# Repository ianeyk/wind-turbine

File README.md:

# wind-turbine
Working repo for summer research on the Just Energy Hub wind turbine design.

## GitHub Repo Index
* **Small_wind_turbine**
    * **3_phase_generator_buck_converter.plecs:** Main working PLECS model for the small turbine buck converter
    * **Frequency_analysis_buck_converter**
        * Contains four additional PLECS models which were used to run bode plots for designing the compensator circuit for the small wind turbine.
    * **Small_turbine_buck_converter_parameters**
        * **Buck_converter_parameters.ipynb:** Jupyter Notebook containing calculations for the inductor value and compensator circuit.
        * **Buck_converter_parameters.html:** Exported HTML of same Notebook
        * **Buck_converter_parameters.pdf:** Exported PDF of same Notebook
        * **Plecs_helper.py:** Library of helper functions used in the Notebook
    * **Small_buck_converter_design_calculations**
        * **Design_calculations.ipynb, html, pdf:** Secondary notebook for calculating such things as how much current the turbine can supply at safe rotation speeds, specs for the input capacitance value, slew rate to ensure the diff amps can respond fast enough, and resistor values for the indicator LEDs.
    * **KiCAD:** Contains the schematic and layout for the small-scale buck converter PCB board which I designed and manufactured over the summer.
* **Large_wind_turbine**
    * **siemens_model_buck_converter_v1.plecs:** Main working PLECS model for the large turbine buck converter, including the 1FW3208-1EE model of the physical generator. The only things that are different between this model and the small_wind_turbine model are the inductor value, compensator values, and perhaps the input capacitance.
     * **1_kv_3phase_generator_buck_converter.plecs:** Older model without using the 1FW3208-1EE model.
    * **Frequency_analysis_buck_converter**
        * Contains four additional PLECS models which were used to run bode plots for designing the compensator circuit for the large wind turbine.
    * **Large_turbine_buck_converter_parameters**
        * **Buck_converter_parameters.ipynb:** Jupyter Notebook containing calculations for the inductor value and compensator circuit.
        * **Minimum_conversion_ratio.ipynb:** Jupyter Notebook containing calculations for the minimum switching time given a 1kV-12V buck converter voltage ratio. I concluded that this is perfectly feasible given a 10kHz switching frequency.
    * **KiCAD:** Folder containing duplicates of the small wind turbine KiCAD files. I was going to start with a copy and modify it, but I never got around to starting it.
    * **LTspice:** Contains a single LTspice model verifying that the bootstrap gate driver will work.
* **Generic_wind_turbine**
    * Earlier exploratory work which served as a template for the above analyses. It should probably be moved to the Archive folder.
* **Measurements_and_calculations**
    * **Battery_measurements**
        * **Battery_resistance.ipynb, .html, .pdf:** Jupyter Notebook analyzing a small set of data I took on our 12V marine batteries in the lab to quantify the internal resistance.
    * **Generator_volage**
        * **Generator_voltage.ipynb, .html, .pdf:** Jupyter Notebook plotting the results of putting the small test turbine in front of the wind tunnel. It calculates the frequency and voltage amplitude at various wind speeds.
    * **Large_turbine_power_predictions**
        * **Large_turbine_power_predictions.ipyny, .html, .pdf:** Jupyter Notebook and exported versions analyzing the power generation data from one of the Eastern Wind Power documents as well as a PLECS model for the generator and the anemometer data from Olin's campus. I recommend a cut-out wind speed of 12m/s for the large turbine.
* **Charge_controller_code**
    * **Platformio.ini:** Platformio project for code running on the Adafruit Feather Adalogger board attached to the small-scale buck converter PCB I designed and manufactured this summer.
    * **src/main.cpp:** Main code file containing Arduino language to be uploaded to the Feather.
* **Archive**
    * **Generator_internal_resistance**
        * **Internal_resistance.ipynb, .html, .pdf:** Jupyter Notebook for an initial experiment determining the internal resistance of the small generator by hand-spinning the small turbine and watching the frequency and voltage decay as it slowed down. The internal resistance calculations match those in *Generator_voltage.ipynb*, and that notebook also has further relevant calculations. Hence this notebook is in the archive.

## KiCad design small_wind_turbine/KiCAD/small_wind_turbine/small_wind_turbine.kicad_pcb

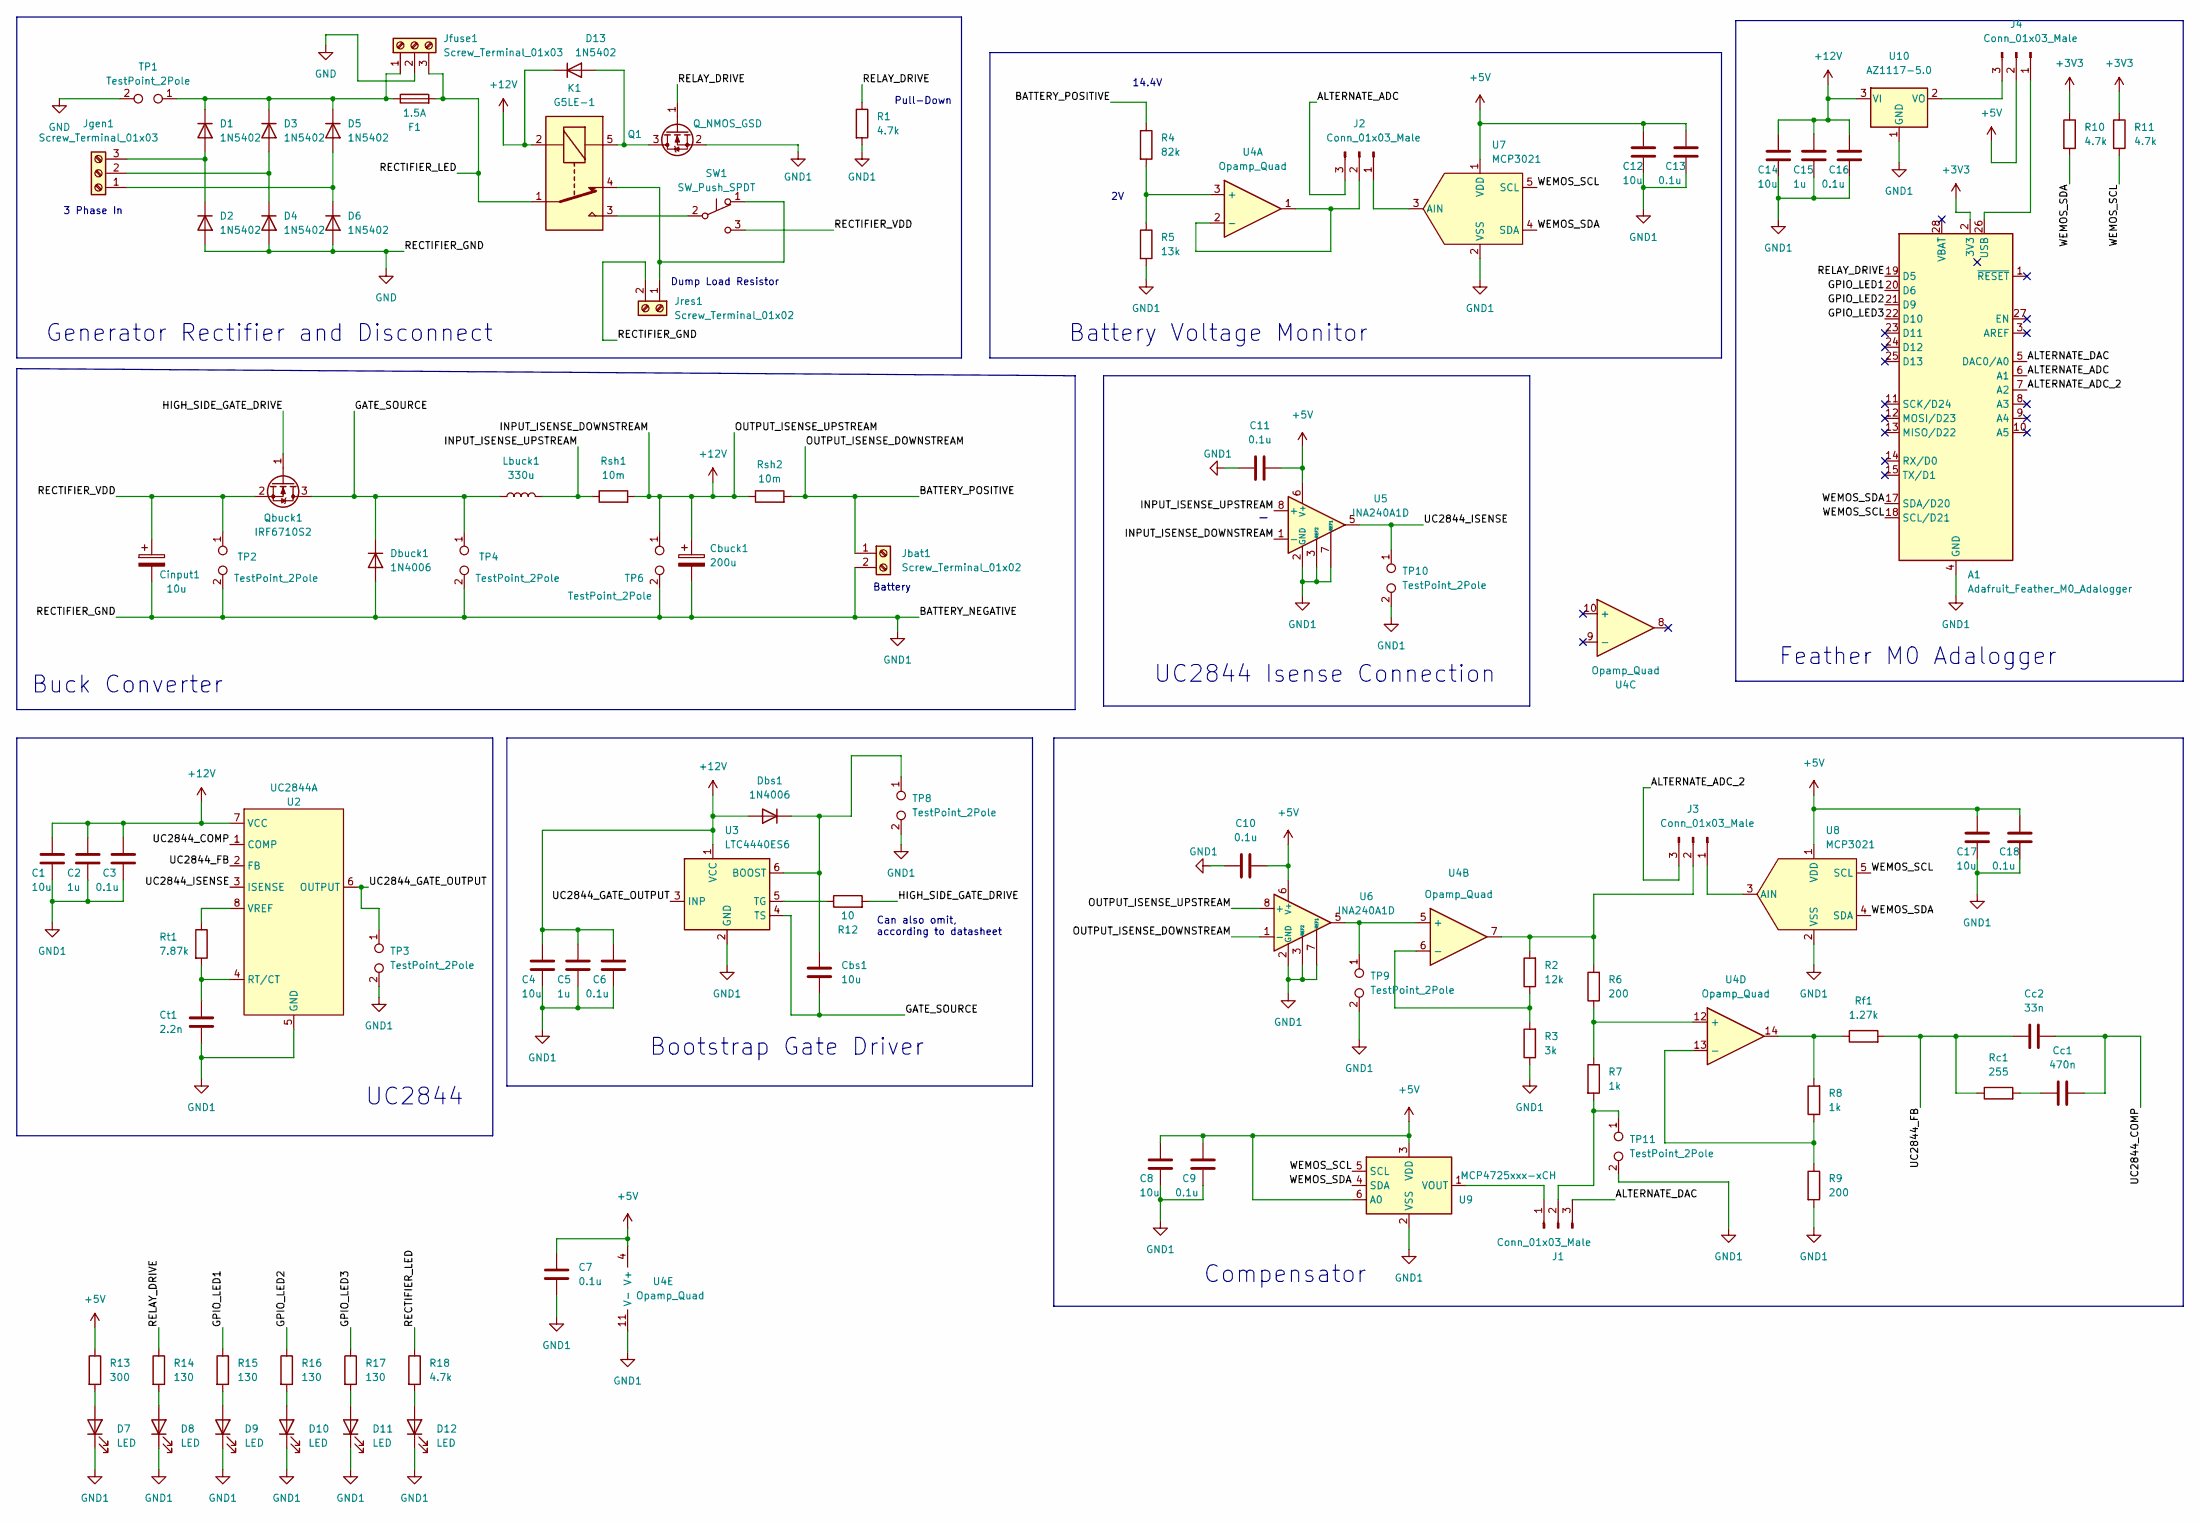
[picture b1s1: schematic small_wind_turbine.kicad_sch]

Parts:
A1: Adafruit_Feather_M0_Adalogger; Adafruit_Feather
C1, C4, C8, C12, C14, C17: 10u; C_0805_2012Metric
C2, C5, C15: 1u; C_0805_2012Metric
C3, C6, C7, C9, C10, C11, C13, C16, C18: 0.1u; C_0805_2012Metric
Cbs1: 10u; CP_Radial_D8.0mm_P3.50mm
Cbuck1: 200u; CP_Radial_D12.5mm_P5.00mm
Cc1: 470n; C_0805_2012Metric
Cc2: 33n; C_0805_2012Metric
Cinput1: 10u; CP_Radial_D6.3mm_P2.50mm
Ct1: 2.2n; C_0805_2012Metric
D1, D2, D3, D4, D5, D6: 1N5402; TO-277A_custom
D7, D8, D9, D10, D11, D12: LED; LED_0603_1608Metric
D13: 1N5402; SOD-323-EP_custom
Dbs1: 1N4006; TO-277A_custom
Dbuck1: 1N4006; TO-277A_custom
F1: 1.5A; FUSE_4527
J1, J2, J3, J4: Conn_01x03_Male; PinHeader_1x03_P2.54mm_Vertical
Jbat1: Screw_Terminal_01x02; CUI_TBP01R1-508-02BE
Jfuse1: Screw_Terminal_01x03; CUI_TBP01R1-508-03BE_no_extra
Jgen1: Screw_Terminal_01x03; CUI_TBP01R1-508-03BE
Jres1: Screw_Terminal_01x02; CUI_TBP01R1-508-02BE
K1: G5LE-1; Relay_SPDT_Omron_G5LE-1
Lbuck1: 330u; smd_inductor
Q1: Q_NMOS_GSD; SOT-23
Qbuck1: IRF6710S2; TO-220-3_Vertical
R1, R10, R11, R18: 4.7k; R_0805_2012Metric
R2: 12k; R_0805_2012Metric
R3: 3k; R_0805_2012Metric
R4: 82k; R_0805_2012Metric
R5: 13k; R_0805_2012Metric
R6, R9: 200; R_0805_2012Metric
R7, R8: 1k; R_0805_2012Metric
R12: 10; R_0805_2012Metric
R13: 300; R_0805_2012Metric
R14, R15, R16, R17: 130; R_0805_2012Metric
Rc1: 255; R_0805_2012Metric
Rf1: 1.27k; R_0805_2012Metric
Rsh1, Rsh2: 10m; R_1206_3216Metric
Rt1: 7.87k; R_0805_2012Metric
SW1: SW_Push_SPDT; manual_switch
TP1, TP2, TP3, TP4, TP6, TP8, TP9, TP10, TP11: TestPoint_2Pole; Oscilloscope_Test_Point
U2: UC2844A; SOIC-8_3.9x4.9mm_P1.27mm
U3: LTC4440ES6; SOT-23-6
U4: Opamp_Quad; SOIC-14_3.9x8.7mm_P1.27mm
U5, U6: INA240A1D; SOIC-8_3.9x4.9mm_P1.27mm
U7, U8: MCP3021; SOT-23-5
U9: MCP4725xxx-xCH; SOT-23-6
U10: AZ1117-5.0; SOT-223-3_TabPin2

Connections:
+3V3: A1.2 (3V3), R10.1, R11.1
+5V: C7.1, C8.1, C9.1, C10.2, C11.2, C12.1, C13.1, C17.1, C18.1, J4.2, R13.1, U4.4 (V+), U5.6 (V+), U6.6 (V+), U7.1 (VDD), U8.1 (VDD), U9.3 (VDD), U9.6 (A0)
+12V: C1.1, C2.1, C3.1, C4.1, C5.1, C6.1, C14.1, C15.1, C16.1, Cbuck1.1, D13.1 (K), Dbs1.2 (A), K1.2, Rsh1.2, Rsh2.1, TP6.1, U2.7 (VCC), U3.1 (VCC), U5.1 (-), U6.8 (+), U10.3 (VI)
/ALTERNATE_ADC: A1.6 (A1), J2.3
/ALTERNATE_ADC_2: A1.7 (A2), J3.3
/ALTERNATE_DAC: A1.5 (DAC0/A0), J1.3
/BATTERY_POSITIVE: Jbat1.1, R4.1, Rsh2.2, U6.1 (-)
/GATE_SOURCE: Cbs1.2, Dbuck1.1 (K), Lbuck1.1, Qbuck1.3 (D), TP4.1, U3.4 (TS)
/GPIO_LED1: A1.20 (D6), R15.1
/GPIO_LED2: A1.21 (D9), R16.1
/GPIO_LED3: A1.22 (D10), R17.1
/HIGH_SIDE_GATE_DRIVE: Qbuck1.1 (G), R12.2
/INPUT_ISENSE_UPSTREAM: Lbuck1.2, Rsh1.1, U5.8 (+)
/RECTIFIER_LED: F1.2, Jfuse1.3, K1.1, R18.1
/RECTIFIER_VDD: Cinput1.1, Qbuck1.2 (S), SW1.3 (C), TP2.1
/RELAY_DRIVE: A1.19 (D5), Q1.1 (G), R1.1, R14.1
/UC2844_COMP: Cc1.2, Cc2.1, U2.1 (COMP)
/UC2844_FB: Cc2.2, Rc1.1, Rf1.2, U2.2 (FB)
/UC2844_GATE_OUTPUT: TP3.1, U2.6 (OUTPUT), U3.3 (INP)
/UC2844_ISENSE: TP10.1, U2.3 (ISENSE), U5.5
/WEMOS_SCL: A1.18 (SCL/D21), R11.2, U7.5 (SCL), U8.5 (SCL), U9.5 (SCL)
/WEMOS_SDA: A1.17 (SDA/D20), R10.2, U7.4 (SDA), U8.4 (SDA), U9.4 (SDA)
GND: A1.4 (GND), A1.16 (GND), C1.2, C2.2, C3.2, C4.2, C5.2, C6.2, C7.2, C8.2, C9.2, C10.1, C11.1, C12.2, C13.2, C14.2, C15.2, C16.2, C17.2, C18.2, Cbuck1.2, Cinput1.2, Ct1.2, D2.2 (A), D4.2 (A), D6.2 (A), D7.1 (K), D8.1 (K), D9.1 (K), D10.1 (K), D11.1 (K), D12.1 (K), Dbuck1.2 (A), Jbat1.2, Jfuse1.2, Jres1.2, Q1.2 (S), R1.2, R3.1, R5.2, R9.2, TP1.2, TP2.2, TP3.2, TP4.2, TP6.2, TP8.2, TP9.2, TP10.2, TP11.2, U2.5 (GND), U3.2 (GND), U4.11 (V-), U5.2 (GND), U5.3 (REF2), U5.4 (GND), U5.7 (REF1), U6.2 (GND), U6.3 (REF2), U6.4 (GND), U6.7 (REF1), U7.2 (VSS), U8.2 (VSS), U9.2 (VSS), U10.1 (GND)
unnamed: A1.26 (USB), J4.1
unnamed: Cbs1.1, Dbs1.1 (K), TP8.1, U3.6 (BOOST)
unnamed: Cc1.1, Rc1.2
unnamed: Ct1.1, Rt1.2, U2.4 (RT/CT)
unnamed: D1.1 (K), D3.1 (K), D5.1 (K), F1.1, Jfuse1.1, TP1.1
unnamed: D1.2 (A), D2.1 (K), Jgen1.3
unnamed: D3.2 (A), D4.1 (K), Jgen1.2
unnamed: D5.2 (A), D6.1 (K), Jgen1.1
unnamed: D7.2 (A), R13.2
unnamed: D8.2 (A), R14.2
unnamed: D9.2 (A), R15.2
unnamed: D10.2 (A), R16.2
unnamed: D11.2 (A), R17.2
unnamed: D12.2 (A), R18.2
unnamed: D13.2 (A), K1.5, Q1.3 (D)
unnamed: J1.1, U9.1 (VOUT)
unnamed: J1.2, R7.2, TP11.1
unnamed: J2.1, U7.3 (AIN)
unnamed: J2.2, U4.1, U4.2 (-)
unnamed: J3.1, U8.3 (AIN)
unnamed: J3.2, R2.2, R6.2, U4.7
unnamed: J4.3, U10.2 (VO)
unnamed: Jres1.1, K1.4, SW1.1 (A)
unnamed: K1.3, SW1.2 (B)
unnamed: R2.1, R3.2, U4.6 (-)
unnamed: R4.2, R5.1, U4.3 (+)
unnamed: R6.1, R7.1, U4.12 (+)
unnamed: R8.1, R9.1, U4.13 (-)
unnamed: R8.2, Rf1.1, U4.14
unnamed: R12.1, U3.5 (TG)
unnamed: Rt1.1, U2.8 (VREF)
unnamed: TP9.1, U4.5 (+), U6.5

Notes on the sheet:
Bootstrap Gate Driver
Can also omit, according to datasheet
UC2844
14.4V
UC2844 Isense Connection
Pull-Down
Generator Rectifier and Disconnect
Compensator
Battery Voltage Monitor
Buck Converter
Battery
3 Phase In
Dump Load Resistor
Feather M0 Adalogger

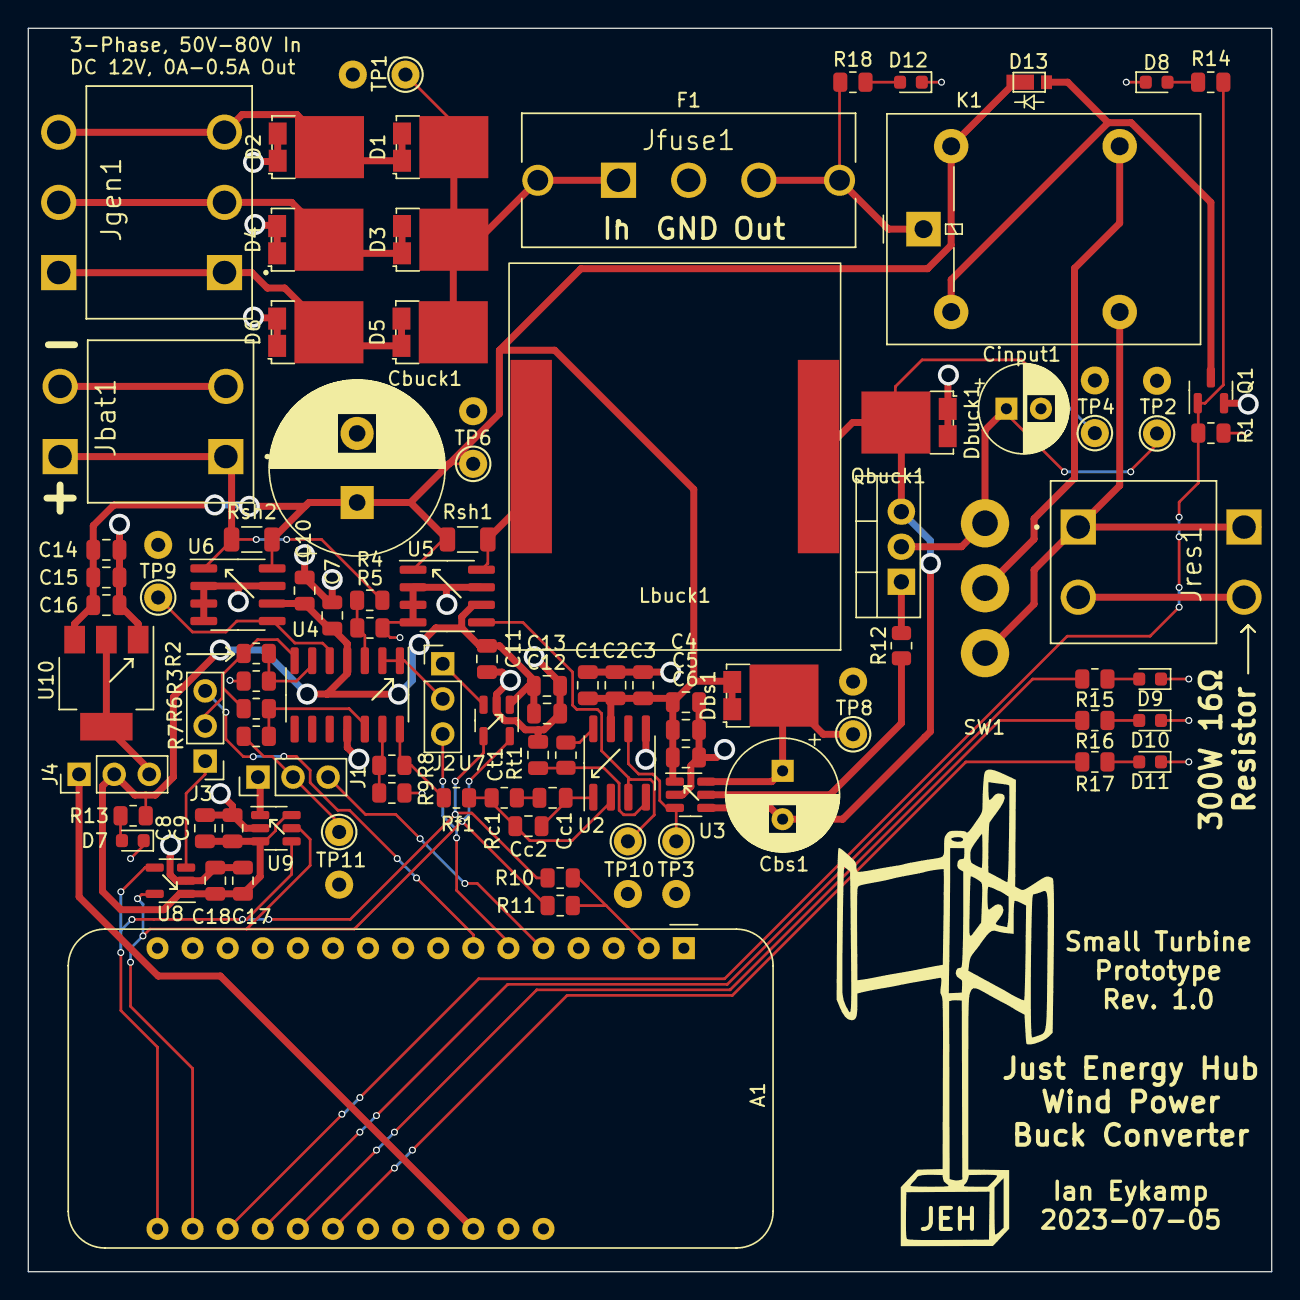
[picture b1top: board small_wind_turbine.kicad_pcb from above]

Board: 2 copper layers, 90.0 x 90.0 mm, 97 parts (1 on the bottom side), 55 nets.

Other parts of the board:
Gen: LOGO; buck_converter_schematic_2
JEH: LOGO; h_rotor_design_3

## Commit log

2023-06-14 initial commit from first three weeks
2023-06-14 plot all transfer functions
2023-06-14 add images and rough draft introduction
2023-06-14 finish first draft
2023-06-14 update buck converter schematic; make it beautiful
2023-06-15 finish buck converter analysis
2023-06-15 plot unrectified generator data
2023-06-15 janky code to calculate internal resistance
2023-06-16 finish internal resistance write-up
2023-06-16 publish internal resistance write-up
2023-06-16 re-run script
2023-06-19 plot maximum power test oscilloscope data
2023-06-19 copy, rename, and update buck converter model for small turbine 3 phase generator
2023-06-19 update values in buck converter analysis notebook for small wind turbine plecs model
2023-06-19 wip updating parameters
2023-06-19 make copy of and rename buck converter parameter notebooks
2023-06-20 update small turbine parameters
2023-06-20 add battery internal resistance measurements
2023-06-21 completely revamp folder structure
2023-06-21 wip refactoring text
2023-06-21 start KiCAD schematic and create UC2844A symbol
2023-06-21 add max power calculation
2023-06-21 wip schematic
2023-06-21 finish current sensing feedback circuit
2023-06-22 add high side gate driver and connect common grounds
2023-06-22 wip schematic. Replace inverting adder with non-inverting adder. Postulate on replacing Isense resistor for UC2844
2023-06-23 mostly update compensator values; slight mismatch with open loop transfer function
2023-06-23 increase time step and play with compensator values
2023-06-23 implement 200uF compensator values in original design; it works
2023-06-23 test bootstrap capacitor theory
2023-06-25 tidy KiCAD schematic
2023-06-25 compare old vs. new compensator values before and after compensating for discrepancy
2023-06-26 increase current to 500mA, re-run simulations, and it works! Also tidy up schematics
2023-06-26 re-organize plecs data csv and schematic files
2023-06-26 clean up and annotate schematic
2023-06-27 export to pdf
2023-06-27 add description document
2023-06-27 add gate resistor and source connection to gate driver
2023-06-27 clean up buck converter parameter writeup
2023-06-27 publish all design write-ups (1)
2023-06-29 after design review: calculate and add input capacitance
2023-06-29 remove extra low-side switch and shunt
2023-06-29 substitute different diff amp with 20V/V gain
2023-06-29 update KiCAD resistor values to match PLECS model
2023-06-30 start adding footprints and bypass capacitors
2023-06-30 finish assigning IC footprints and bypass capacitance. All IC footprints are double-checked.
2023-06-30 wip assigning passives footprints
2023-06-30 wip adding footprints (2)
2023-06-30 wip adding footprints (3)
2023-06-30 wip adding footprints (4)
2023-06-30 finish assigning footprints
2023-06-30 add BOM
2023-06-30 add test points galore
2023-06-30 start layout (1)
2023-06-30 wip layout (2)
2023-07-03 wip layout (3)
2023-07-03 wip layout (4)
2023-07-03 wip layout (5)
2023-07-03 wip layout (6)
2023-07-03 wip layout (7)
2023-07-04 move test points close to proper locations
2023-07-04 finalize relative positions; ready to start finessing
2023-07-04 finish finessing placement
2023-07-04 wip laying traces
2023-07-04 wip laying traces (2)
2023-07-04 almost finished laying traces
2023-07-04 finish laying traces
2023-07-04 finish connecting ground vias
2023-07-04 improve ground plane near relay
2023-07-05 replace terminal blocks and add silkscreen design
2023-07-05 replace 'Ohm' with Omega symbol
2023-07-05 add 3d models and fix transistor pin ordering
2023-07-05 tweak aesthetics
2023-07-05 add jumper to switch 5V rail
2023-07-05 change position of J4 label
2023-07-06 fix Q1 pin ordering
2023-07-06 add optional fuse terminal block
2023-07-06 add relay protection flyback diode
2023-07-06 re-zip files for review (2)
2023-07-07 download final bom from spreadsheet
2023-07-10 submit Gerbers to manufacturer
2023-07-10 first pass large wind turbine PLECS model; working control loop, slightly underdamped
2023-07-18 working ADC I2C code
2023-07-18 begin large wind turbine exploration
2023-07-18 working DAC I2C control
2023-07-20 plot anemometer data
2023-07-22 continue max power calculations
2023-07-26 add explanation of wind speed resources
2023-07-26 add anemometer data analysis
2023-07-26 create parameter sweep of resistance and angular velocity of generator in PLECS
2023-07-27 tabulate final power estimate values from various sources
2023-07-27 finish write-up of maximum power estimation
2023-07-27 re-run plecs model, add assumptions, and submit report
2023-07-31 fix order of imported datasets; the data make more sense now
2023-07-31 clean up and export small wind generator test data from wind tunnel
2023-08-16 update parameter sweep simulation script and calculate dump load voltage
2023-08-16 pork barrel: export notebooks as html and pdf
2023-08-16 rename folders, filenames, and notebook titles
2023-08-16 add github repo index
2023-08-17 move internal_resistance.ipynb to archive and small_buck_converter_design_calculations.ipynb to small_wind_turbine folder
2023-08-25 create new version of large buck converter calculations with correctly performing control loop
